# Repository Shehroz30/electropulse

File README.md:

# Electropulse

A custom, homemade, low voltage, simple TENs device

## Features
* ESP32-C3 Microntroller with Bluetooth
* Wireless control
* WiFi controlled
* USB-C powered
* Low-cost - total BOM + board ~$11.56 per board
* Two output channels
* Modular + fits with different electrode types
* Two buck boosts for efficiency
* BJT controlled current limiter

## Build
The build of this device is extremely uncomplicated. Use M3 0.5 inch screws for the enclosure and M2 0.315 inch screws for mounting the PCB. The electrodes can simply be attached to the Pin Headers.

A link to the Onshape file can be found [here](https://cad.onshape.com/documents/0b9b685ed737be4511598f4a/w/ba1d33f46afe7a8ff807ef53/e/736e59d6b3c7b8673a0b7fd8?renderMode=0&uiState=69ea24d6e717aaec3b4bf4c2)

## Use
* Flash the code onto the ESP32 using Arduino IDE
* Go to http://\<ESP-32\_IP\>/
* Connect your electrodes to the pin headers

## Motivation
I made this project because I've been struggling a little bit with knee pain and I found that other options on the market weren't as adjustable. I also had electrodes lying around (due to a separate business pitch project) and I wanted to make use of them

## BOM
To use this device, electrodes are a requirement. To purchase these, you can go to Amazon at [this link](https://www.amazon.com/Best-Sellers-Electrodes/zgbs/industrial/3013606011)

| Designator               | Footprint       |   Quantity | Value                | LCSC Part   | Link                                               |
|:-------------------------|:----------------|-----------:|:---------------------|:------------|:---------------------------------------------------|
| C1,C2,C3,C4              | 1206            |          8 | 4.7uF                | C29823      | https://www.lcsc.com/product-detail/C29823.html    |
| C5                       | 0603            |          2 | 0.047uF              | C1622       | https://www.lcsc.com/product-detail/C1622.html     |
| C8                       | 1206            |          2 | 10uF                 | C13585      | https://www.lcsc.com/product-detail/C13585.html    |
| C10,C11,C12,C13,C6,C7,C9 | 0603            |         18 | 0.1uF                | C14663      | https://www.lcsc.com/product-detail/C14663.html    |
| C18,C23                  | 0603            |        4   | 100nf                | C14663      | https://www.lcsc.com/product-detail/C14663.html    |
| C21,C22                  | 0605            |          4 | 10uf                 | C19702      | https://www.lcsc.com/product-detail/C19702.html    |
| C25,C26,C27              | 0805            |          6 | 22uf                 | C45783      | https://www.lcsc.com/product-detail/C45783.html    |
| D1                       | SMA(DO-214AC)   |          2 | D_Schottky           | C8678       | https://www.lcsc.com/product-detail/C8678.html     |
| D2                       | 0603            |          2 | LED                  | C2290       | https://www.lcsc.com/product-detail/C2290.html     |
| D4                       | SOT-23-6L       |          5 | USBLC6-2SC6          | C7519       | https://www.lcsc.com/product-detail/C7519.html     |
| J1                       | 插件,P=2.54mm     |          4 | Conn_01x02           | C32713268   | https://www.lcsc.com/product-detail/C32713268.html |
| J5                       | SMD             |          5 | MC-311D              | C136423     | https://www.lcsc.com/product-detail/C136423.html   |
| L1                       | 1008            |          5 | 2.2uH                | C86092      | https://www.lcsc.com/product-detail/C86092.html    |
| L2                       | SMD,7.2x6.6mm   |          5 | 10uH                 | C5189958    | https://www.lcsc.com/product-detail/C5189958.html  |
| Q2,Q4                    | SOT-23          |         10 | MMBT2222A            | C7420351    | https://www.lcsc.com/product-detail/C7420351.html  |
| Q3,Q5                    | SOT-223         |          5 | FZT853TA             | C435890     | https://www.lcsc.com/product-detail/C435890.html   |
| R1                       | 0603            |          2 | 250k                 | C22961      | https://www.lcsc.com/product-detail/C22961.html    |
| R2                       | 0603            |          2 | 330                  | C23138      | https://www.lcsc.com/product-detail/C23138.html    |
| R6                       | 0603            |          2 | 75k                  | C23242      | https://www.lcsc.com/product-detail/C23242.html    |
| R7                       | 0603            |          2 | 2k                   | C22975      | https://www.lcsc.com/product-detail/C22975.html    |
| R10,R14,R3               | 0603            |          6 | 10k                  | C25804      | https://www.lcsc.com/product-detail/C25804.html    |
| R11,R9                   | 0603            |          4 | 5.1k                 | C23186      | https://www.lcsc.com/product-detail/C23186.html    |
| R13,R19                  | 0603            |          4 | 14                   | C22950      | https://www.lcsc.com/product-detail/C22950.html    |
| R15                      | 0603            |          2 | 1M                   | C22935      | https://www.lcsc.com/product-detail/C22935.html    |
| R16                      | 0603            |         20 | 180k                 | C22827      | https://www.lcsc.com/product-detail/C22827.html    |
| R17,R18                  | 0603            |          4 | 1K                   | C21190      | https://www.lcsc.com/product-detail/C21190.html    |
| SW1,SW3                  | SMD,4x3mm       |          4 | TS-1088-AR02016      | C720477     | https://www.lcsc.com/product-detail/C720477.html   |
| U1                       | VFQFN-32-EP     |          2 | ESP32-C3-WROOM-02-N4 | C2934560    | https://www.lcsc.com/product-detail/C2934560.html  |
| U2                       | WQFN-16-EP(3x3) |          2 | TPS55340RTER         | C169167     | https://www.lcsc.com/product-detail/C169167.html   |
| U5                       | VSON-14-EP(3x4) |          2 | TPS63020DSJR         | C15483      | https://www.lcsc.com/product-detail/C15483.html    |

## JLCBPCB Order
For two assembled PCBs, the cost is around ~70$ for the cheapest shipping option. Keep in mind that there are a lot of alternatives to the parts selected, so ifsomething is unavailable you can easily change them around within the JLCPCB assembly order.

## Firmware

The code is written using Arduino IDE compiled for an ESP32-C3. Please note that the local host where the web page is hosted depends entirely on your ESP32, so it may not be the same for everyone. Also be sure to input your wifi credentials when flashing so that the ESP32 can connect to WiFi. 

## Fallout Zine Poster

## Thanks

Huge thanks to HackClub for helping me with this project!

## Verfication
Hack Club Username: shehrozmaan4

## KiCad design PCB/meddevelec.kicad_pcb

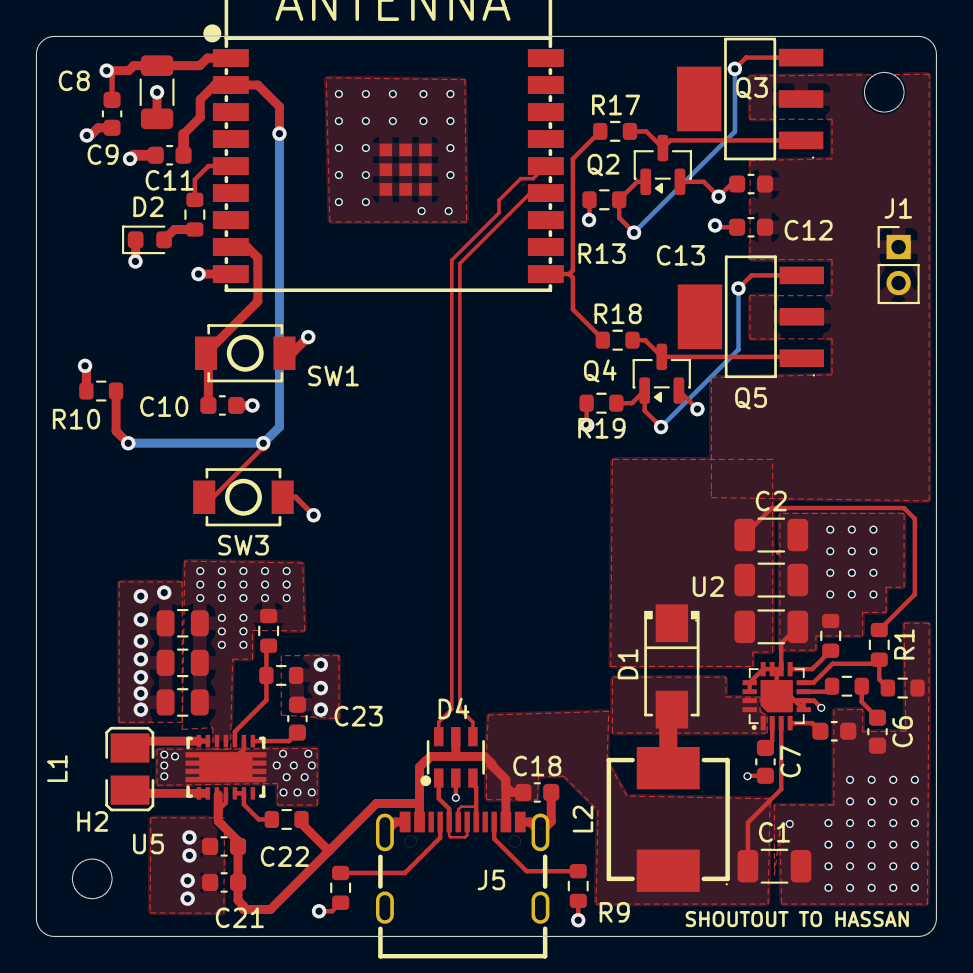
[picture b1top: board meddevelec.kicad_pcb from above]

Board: 4 copper layers, 50.0 x 50.0 mm, 55 parts (0 on the bottom side), 31 nets.

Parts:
C1, C2, C3, C4: 4.7uF; C_1206_3216Metric
C5: 0.047uF; C_0603_1608Metric
C6, C7, C9, C10, C11, C12, C13: 0.1uF; C_0603_1608Metric
C8: 10uF; C_1206_3216Metric
C18, C23: 100nf; C_0603_1608Metric
C21, C22: 10uf; C_0603_1608Metric
C25, C26, C27: 22uf; C_0805_2012Metric
D1: D_Schottky; SMA_L4.3-W2.7-LS5.1-RD
D2: LED; LED_0603_1608Metric
D4: USBLC6-2SC6; SOT-23-6_L2.9-W1.6-P0.95-LS2.8-BL
H1, H2, H3, H4: MountingHole; MountingHole_2.2mm_M2
J1: Conn_01x02; PinHeader_1x02_P2.00mm_Vertical
J5: MC-311D; USB-C-SMD_MC-311D
L1: 2.2uH; L1008
L2: 10uH; IND-SMD_L7.2-W6.6_GPSR07X0
Q2, Q4: MMBT2222A; SOT-23
Q3, Q5: FZT853TA; SOT-223-4_L6.5-W3.5-P2.30-LS7.0-BR
R1: 250k; R_0603_1608Metric
R2: 330; R_0603_1608Metric
R3, R10, R14: 10k; R_0603_1608Metric
R6: 75k; R_0603_1608Metric
R7: 2k; R_0603_1608Metric
R9, R11: 5.1k; R_0603_1608Metric
R13, R19: 14; R_0603_1608Metric
R15: 1M; R_0603_1608Metric
R16: 180k; R_0603_1608Metric
R17, R18: 1K; R_0603_1608Metric
SW1, SW3: TS-1088-AR02016; SW-SMD_L3.9-W3.0-P4.45
U1: ESP32-C3-WROOM-02-N4; BULETM-SMD_ESPRESSIF_ESP32-C3-WROOM-02-N4-4MB
U2: TPS55340RTER; VQFN-16_L3.0-W3.0-P0.50-BL-EP1.7
U5: TPS63020DSJR; VSON-14_L4.0-W3.0-P0.50-BL-EP_TI_DSJ

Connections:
+3.3V: C8.1, C9.1, C25.1, C26.1, C27.1, R10.1, R15.1, U1.1 (3V3), U5.4 (VOUT), U5.5 (VOUT)
+5V: C1.1, C18.1, C21.1, C22.1, D4.5, J5.A4-B9 (VBUS), J5.B4-A9 (VBUS), L2.1, R14.2, U2.3 (EN), U5.10 (VIN), U5.11 (VIN)
+32V: C2.1, C3.1, C4.1, C12.1, C13.1, D1.1 (K), J1.1, J1.2, Q3.2 (C), Q5.2 (C), R1.1
/BOOT: C10.1, SW1.2, U1.8 (IO9)
/D+: D4.4, U1.13 (IO18)
/D-: D4.6, U1.14 (IO19)
/LED: R2.1, U1.5 (IO6)
/PWM_C: R17.1, R18.1, U1.10 (IO10)
/UD+: D4.3, J5.A6 (DP1), J5.B6 (DP2)
/UD-: D4.1, J5.A7 (DN1), J5.B7 (DN2)
GND: C1.2, C2.2, C3.2, C4.2, C5.2, C6.2, C7.2, C8.2, C9.2, C10.2, C11.2, C12.2, C13.2, C18.2, C21.2, C22.2, C23.2, C25.2, C26.2, C27.2, D2.1 (K), D4.2, J5.1 (SHIELD), J5.2 (SHIELD), J5.3 (SHIELD), J5.4 (SHIELD), J5.A1-B12 (GND), J5.B1-A12 (GND), Q2.2 (E), Q4.2 (E), R3.2, R6.2, R9.2, R11.2, R13.2, R16.2, R19.2, SW1.1, SW3.1, U1.9 (GND), U1.19 (EP), U2.5 (SYNC), U2.6 (AGND), U2.10 (NC), U2.11 (PGND), U2.12 (PGND), U2.13 (PGND), U2.14 (NC), U2.17 (EP), U5.2 (GND), U5.15 (PGND)
unnamed: C6.1, R7.2
unnamed: D1.2 (A), L2.2, U2.1 (SW), U2.15 (SW), U2.16 (SW)
unnamed: D2.2 (A), R2.2
unnamed: J5.A5 (CC1), R11.1
unnamed: J5.B5 (CC2), R9.1
unnamed: L1.1, U5.8 (L1), U5.9 (L1)
unnamed: L1.2, U5.6 (L2), U5.7 (L2)
unnamed: Q2.1 (B), Q3.3 (E), R13.1
unnamed: Q2.3 (C), Q3.1 (B), R17.2
unnamed: Q4.1 (B), Q5.3 (E), R19.1
unnamed: Q4.3 (C), Q5.1 (B), R18.2
unnamed: C11.1, R10.2, SW3.2, U1.2 (EN)
unnamed: R7.1, U2.7 (COMP)
unnamed: R1.2, R3.1, U2.8 (FB)
unnamed: R6.1, U2.9 (FREQ)
unnamed: C5.1, U2.4 (SS)
unnamed: C7.1, U2.2 (VIN)
unnamed: R14.1, U5.12 (EN), U5.13 (PS/SYNC)
unnamed: R15.2, R16.1, U5.3 (FB)
unnamed: C23.1, U5.1 (VINA)

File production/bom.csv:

Designator,Footprint,Quantity,Value,LCSC Part #
"C1, C2, C3, C4",1206,4,4.7uF,
"C10, C11, C12, C13, C6, C7, C9",0603,7,0.1uF,
"C18, C23",0603,2,100nf,
"C21, C22",0603,2,10uf,
"C25, C26, C27",0805,3,22uf,
C5,0603,1,0.047uF,
C8,1206,1,10uF,
D1,SMA_L4.3-W2.7-LS5.1-RD,1,D_Schottky,C908680
D2,0603,1,LED,
D4,SOT-23-6_L2.9-W1.6-P0.95-LS2.8-BL,1,USBLC6-2SC6,C7519
J1,PinHeader_1x02_P2.00mm_Vertical,1,Conn_01x02,
J5,USB-C-SMD_MC-311D,1,MC-311D,C136423
L1,L1008,1,2.2uH,
L2,IND-SMD_L7.2-W6.6_GPSR07X0,1,10uH,C5189958
"Q2, Q4",SOT-23,2,MMBT2222A,
"Q3, Q5",SOT-223-4_L6.5-W3.5-P2.30-LS7.0-BR,2,FZT853TA,C435890
R1,0603,1,250k,
"R10, R14, R3",0603,3,10k,
"R11, R9",0603,2,5.1k,
"R13, R19",0603,2,14,
R15,0603,1,1M,
R16,0603,1,180k,
"R17, R18",0603,2,1K,
R2,0603,1,330,
R6,0603,1,75k,
R7,0603,1,2k,
"SW1, SW3",SW-SMD_L3.9-W3.0-P4.45,2,TS-1088-AR02016,C720477
U1,BULETM-SMD_ESPRESSIF_ESP32-C3-WROOM-02-N4-4MB,1,ESP32-C3-WROOM-02-N4,C2934560
U2,VQFN-16_L3.0-W3.0-P0.50-BL-EP1.7,1,TPS55340RTER,C169167
U5,VSON-14_L4.0-W3.0-P0.50-BL-EP_TI_DSJ,1,TPS63020DSJR,C15483

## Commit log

2026-04-22 final parts commit
2026-04-22 fix readme
2026-04-22 added jlcpcb order
2026-04-22 add fallout posters
2026-04-23 fixed bom + readme
2026-04-23 fix bom
2026-05-07 fix project requirements
2026-05-10 add onshape link to readme
